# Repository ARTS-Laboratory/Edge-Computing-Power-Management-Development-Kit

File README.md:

# Edge-Computing-Power-Management-Development-Kit

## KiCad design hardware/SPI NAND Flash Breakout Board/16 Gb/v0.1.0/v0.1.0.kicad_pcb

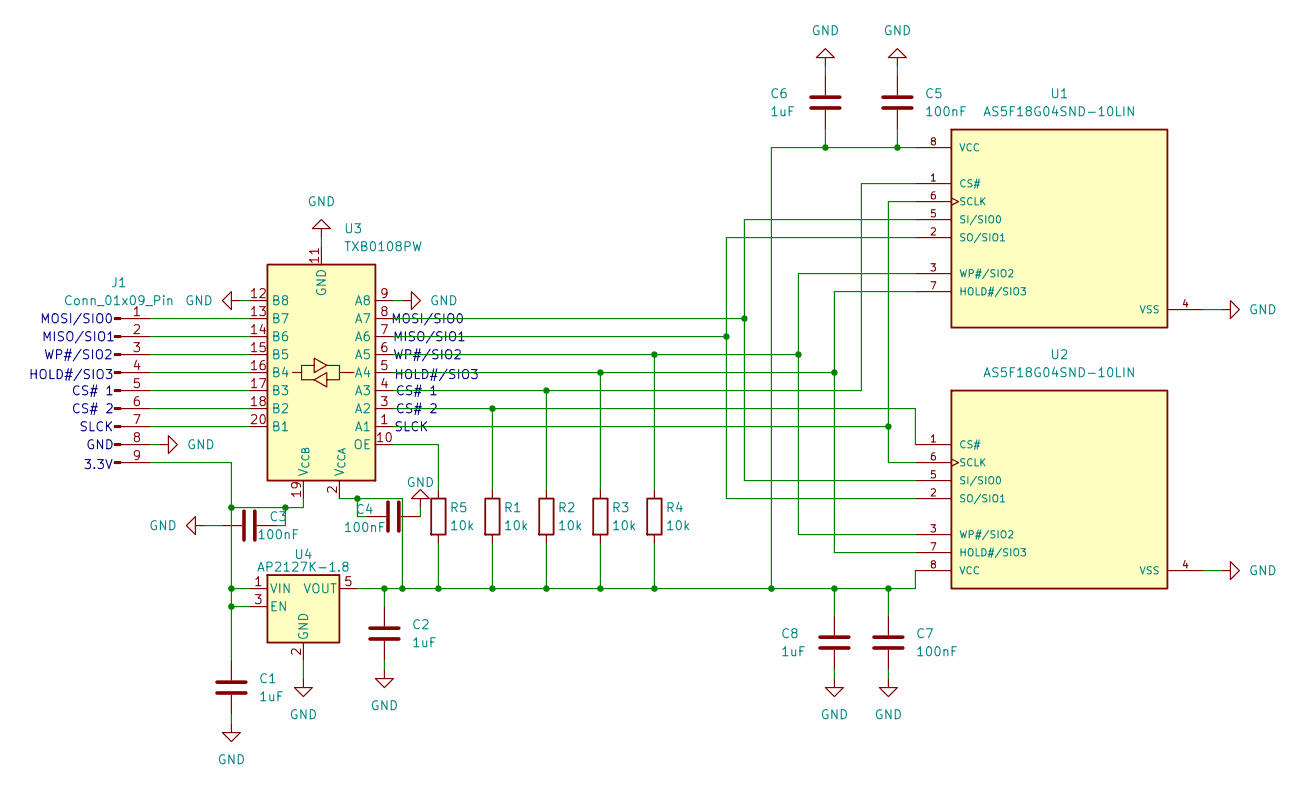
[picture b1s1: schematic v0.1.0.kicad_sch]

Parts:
C1, C2, C6, C8: 1uF; C_0805_2012Metric
C3, C4, C5, C7: 100nF; C_0805_2012Metric
J1: Conn_01x09_Pin; PinSocket_1x09_P2.54mm_Vertical
R1, R2, R3, R4, R5: 10k; R_0805_2012Metric
U1, U2: AS5F18G04SND-10LIN; SON127P600X800X80-8N; PARTREV 1.0; DigiKey_Part_Number 1450-AS5F18G04SND-10LIN-ND
U3: TXB0108PW; TSSOP-20_4.4x6.5mm_P0.65mm
U4: AP2127K-1.8; SOT-23-5

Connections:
GND: C1.2, C2.2, C3.1, C4.1, C5.1, C6.1, C7.2, C8.2, J1.8, U1.4 (VSS), U2.4 (VSS), U3.9 (A8), U3.11 (GND), U3.12 (B8), U4.2 (GND)
unnamed: J1.1, U3.13 (B7)
unnamed: J1.2, U3.14 (B6)
unnamed: J1.3, U3.15 (B5)
unnamed: J1.4, U3.16 (B4)
unnamed: J1.5, U3.17 (B3)
unnamed: J1.6, U3.18 (B2)
unnamed: J1.7, U3.20 (B1)
unnamed: C1.1, C3.2, J1.9, U3.19 (V_{CCB}), U4.1 (VIN), U4.3 (EN)
unnamed: R2.1, U1.1 (CS#), U3.4 (A3)
unnamed: R3.1, U1.7 (HOLD#/SIO3), U2.7 (HOLD#/SIO3), U3.5 (A4)
unnamed: U1.6 (SCLK), U2.6 (SCLK), U3.1 (A1)
unnamed: U1.5 (SI/SIO0), U2.5 (SI/SIO0), U3.8 (A7)
unnamed: U1.2 (SO/SIO1), U2.2 (SO/SIO1), U3.7 (A6)
unnamed: C2.1, C4.2, C5.2, C6.2, C7.1, C8.1, R1.2, R2.2, R3.2, R4.2, R5.2, U1.8 (VCC), U2.8 (VCC), U3.2 (V_{CCA}), U4.5 (VOUT)
unnamed: R4.1, U1.3 (WP#/SIO2), U2.3 (WP#/SIO2), U3.6 (A5)
unnamed: R1.1, U2.1 (CS#), U3.3 (A2)
unnamed: R5.1, U3.10 (OE)

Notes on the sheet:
WP#/SIO2
SLCK
CS# 1
CS# 2
GND
HOLD#/SIO3
MISO/SIO1
MOSI/SIO0
3.3V

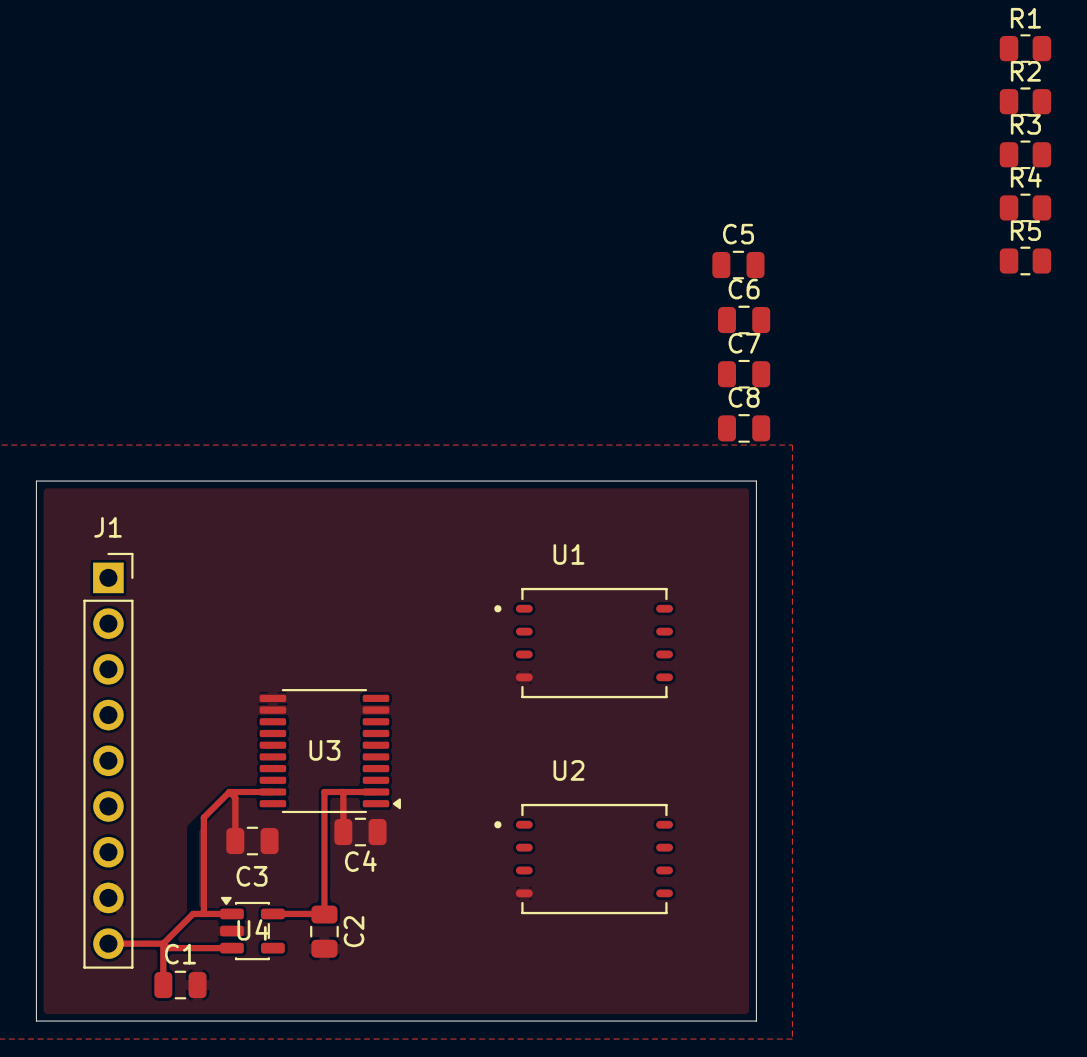
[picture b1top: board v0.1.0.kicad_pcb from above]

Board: 2 copper layers, 40.0 x 30.0 mm, 18 parts (0 on the bottom side), 18 nets.

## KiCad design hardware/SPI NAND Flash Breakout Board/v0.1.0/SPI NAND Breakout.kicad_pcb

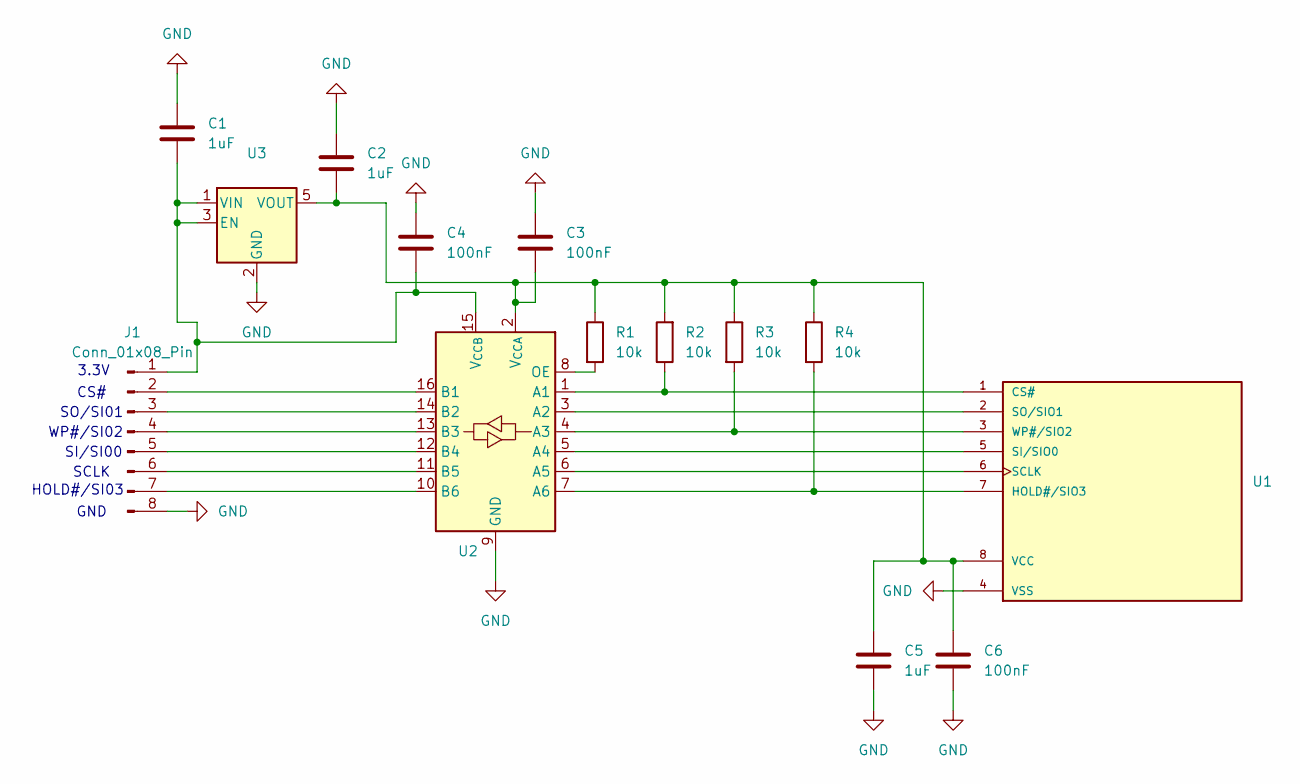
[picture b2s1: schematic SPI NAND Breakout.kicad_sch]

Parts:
C1, C2, C5: 1uF; C_0805_2012Metric
C3, C4, C6: 100nF; C_0805_2012Metric
J1: Conn_01x08_Pin; PinSocket_1x08_P2.54mm_Vertical
R1, R2, R3, R4: 10k; R_0805_2012Metric
U1: AS5F18G04SND-10LIN; SON127P600X800X80-8N; PARTREV 1.0
U2: TXB0106PW; TSSOP-16_4.4x5mm_P0.65mm
U3: AP2127K-1.8; SOT-23-5

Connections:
GND: C1.1, C2.1, C3.1, C4.1, C5.2, C6.2, J1.8, U1.4 (VSS), U2.9 (GND), U3.2 (GND)
unnamed: C1.2, C4.2, J1.1, U2.15 (V_{CCB}), U3.1 (VIN), U3.3 (EN)
unnamed: J1.2, U2.16 (B1)
unnamed: J1.3, U2.14 (B2)
unnamed: J1.4, U2.13 (B3)
unnamed: J1.5, U2.12 (B4)
unnamed: J1.6, U2.11 (B5)
unnamed: J1.7, U2.10 (B6)
unnamed: R2.1, U1.1 (CS#), U2.1 (A1)
unnamed: R4.2, U1.7 (HOLD#/SIO3), U2.7 (A6)
unnamed: U1.6 (SCLK), U2.6 (A5)
unnamed: U1.5 (SI/SIO0), U2.5 (A4)
unnamed: U1.2 (SO/SIO1), U2.3 (A2)
unnamed: C2.2, C3.2, C5.1, C6.1, R1.1, R2.2, R3.1, R4.1, U1.8 (VCC), U2.2 (V_{CCA}), U3.5 (VOUT)
unnamed: R3.2, U1.3 (WP#/SIO2), U2.4 (A3)
unnamed: R1.2, U2.8 (OE)

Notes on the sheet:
SO/SI01
WP#/SI02
SI/SI00
CS#
HOLD#/SI03
GND
3.3V
SCLK

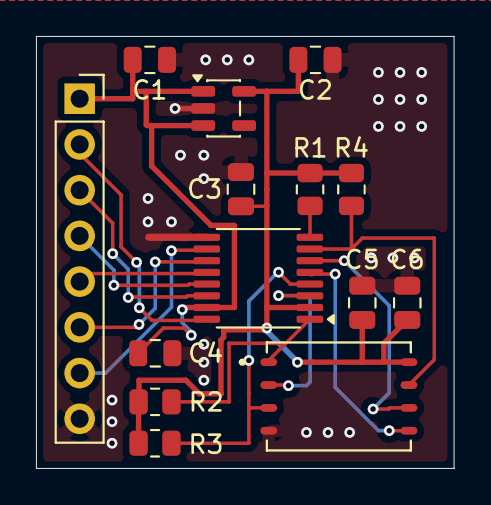
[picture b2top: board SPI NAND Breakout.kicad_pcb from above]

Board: 2 copper layers, 23.2 x 24.0 mm, 14 parts (0 on the bottom side), 16 nets.

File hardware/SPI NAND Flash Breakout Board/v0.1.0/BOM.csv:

Comment ,Designator,Footprint
1uF,"C1,C2,C5",Capacitor_SMD:C_0805_2012Metric
100nF,"C3,C4,C6",Capacitor_SMD:C_0805_2012Metric
Conn_01x08_Pin,J1,Connector_PinSocket_2.54mm:PinSocket_1x08_P2.54mm_Vertical
10k,"R1,R2,R3,R4",Resistor_SMD:R_0805_2012Metric
AS5F18G04SND-10LIN,U1,Breakout:SON127P600X800X80-8N
TXB0106PW,U2,Package_SO:TSSOP-16_4.4x5mm_P0.65mm
AP2127K-1.8,U3,Package_TO_SOT_SMD:SOT-23-5

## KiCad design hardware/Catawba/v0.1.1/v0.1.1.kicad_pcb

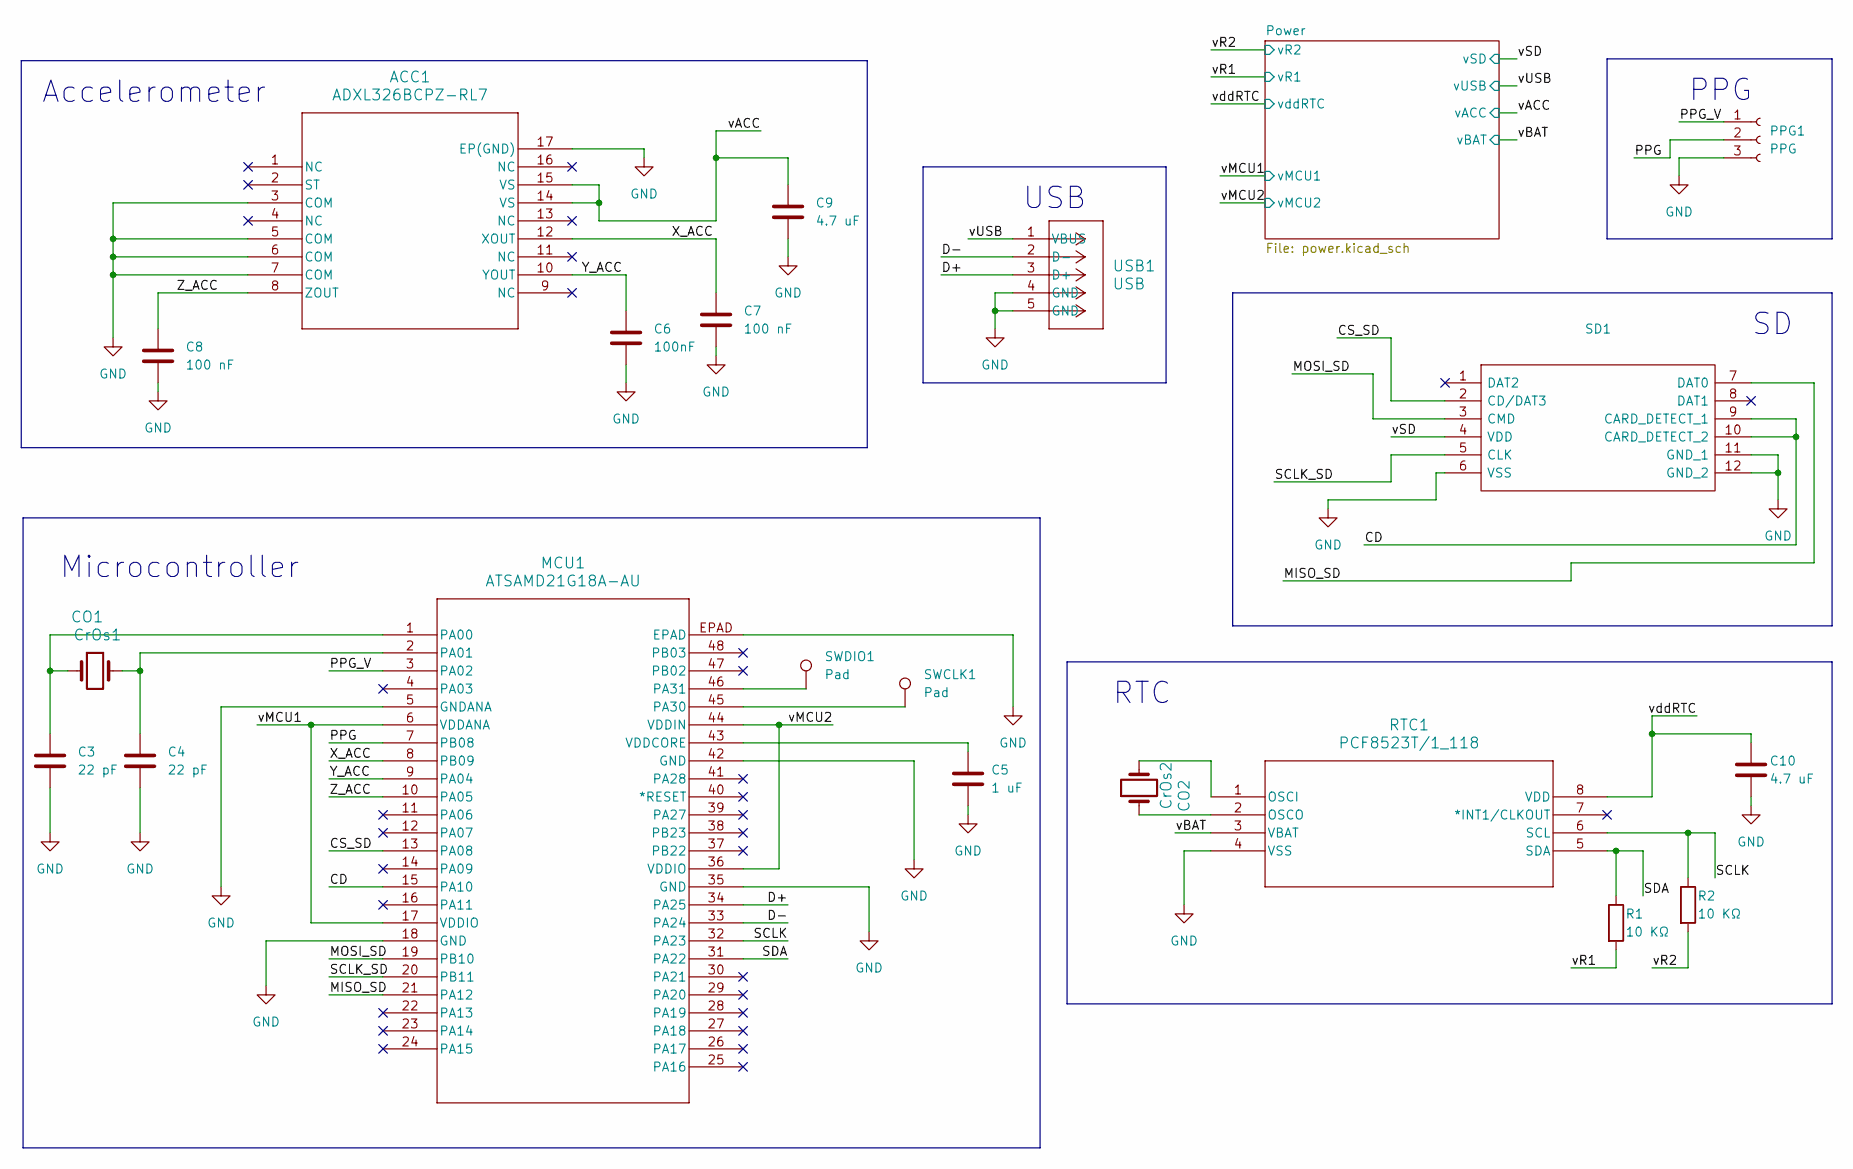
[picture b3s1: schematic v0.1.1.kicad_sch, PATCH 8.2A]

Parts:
ACC1: ADXL326BCPZ-RL7; LFCSP-16-1EP_4x4mm_P0.65mm_EP2.1x2.1mm
C3, C4: 22 pF; C_0603_1608Metric
C5: 1 uF; C_0603_1608Metric
C6: 100nF; C_0603_1608Metric
C7, C8: 100 nF; C_0603_1608Metric
C9, C10: 4.7 uF; C_0603_1608Metric
CO1: CrOs1; XTAL_ABS05-32.768KHZ
CO2: CrOs2; XTAL_ABS05-32.768KHZ
MCU1: ATSAMD21G18A-AU; TQFP-48-1EP_7x7mm_P0.5mm_EP3.5x3.5mm
PPG1: PPG; PinSocket_1x03_P2.54mm_Vertical
R1, R2: 10 KΩ; R_0603_1608Metric
RTC1: PCF8523T/1_118; SOIC-8_3.9x4.9mm_P1.27mm
SD1: TF-00B1; MicroSD_Socket; Manufacturer_Part_Number 1660; Mouser Part Number 485-1660
SWCLK1: Pad; TestPoint_Pad_D2.5mm
SWDIO1: Pad; TestPoint_Pad_D2.5mm
USB1: USB; USB_Micro-B_Molex-105017-0001

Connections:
/CD: MCU1.15 (PA10), SD1.9 (CARD_DETECT_1), SD1.10 (CARD_DETECT_2)
/CS_SD: MCU1.13 (PA08), SD1.2 (CD/DAT3)
/D+: MCU1.34 (PA25), USB1.3 (D+)
/D-: MCU1.33 (PA24), USB1.2 (D-)
/MISO_SD: MCU1.21 (PA12), SD1.7 (DAT0)
/MOSI_SD: MCU1.19 (PB10), SD1.3 (CMD)
/PPG: MCU1.7 (PB08), PPG1.2
/PPG_V: MCU1.3 (PA02), PPG1.1
/SCLK: MCU1.32 (PA23), R2.1, RTC1.6 (SCL)
/SCLK_SD: MCU1.20 (PB11), SD1.5 (CLK)
/SDA: MCU1.31 (PA22), R1.1, RTC1.5 (SDA)
/X_ACC: ACC1.12 (XOUT), C7.1, MCU1.8 (PB09)
/Y_ACC: ACC1.10 (YOUT), C6.1, MCU1.9 (PA04)
/Z_ACC: ACC1.8 (ZOUT), C8.1, MCU1.10 (PA05)
/vACC: ACC1.14 (VS), ACC1.15 (VS), C9.1, C10.1, MCU1.6 (VDDANA), MCU1.17 (VDDIO), MCU1.36 (VDDIO), MCU1.44 (VDDIN), R1.2, R2.2, RTC1.8 (VDD), SD1.4 (VDD); also elsewhere on the board
/vBAT: RTC1.3 (VBAT); also elsewhere on the board
/vUSB: USB1.1 (VBUS); also elsewhere on the board
GND: ACC1.3 (COM), ACC1.5 (COM), ACC1.6 (COM), ACC1.7 (COM), ACC1.17 (EP(GND)), C3.2, C4.2, C5.2, C6.2, C7.2, C8.2, C9.2, C10.2, MCU1.5 (GNDANA), MCU1.18 (GND), MCU1.35 (GND), MCU1.42 (GND), MCU1.EPAD, PPG1.3, RTC1.4 (VSS), SD1.6 (VSS), SD1.11 (GND_1), SD1.12 (GND_2), USB1.4 (GND), USB1.5 (GND); also elsewhere on the board
unnamed: C3.1, CO1.1, MCU1.1 (PA00)
unnamed: C4.1, CO1.2, MCU1.2 (PA01)
unnamed 20: MCU1.45 (PA30), SWCLK1.1; also elsewhere on the board
unnamed 21: MCU1.46 (PA31), SWDIO1.1; also elsewhere on the board
unnamed: C5.1, MCU1.43 (VDDCORE)
unnamed: CO2.2, RTC1.1 (OSCI)
unnamed: CO2.1, RTC1.2 (OSCO)

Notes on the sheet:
PPG
USB
Accelerometer
Microcontroller
RTC

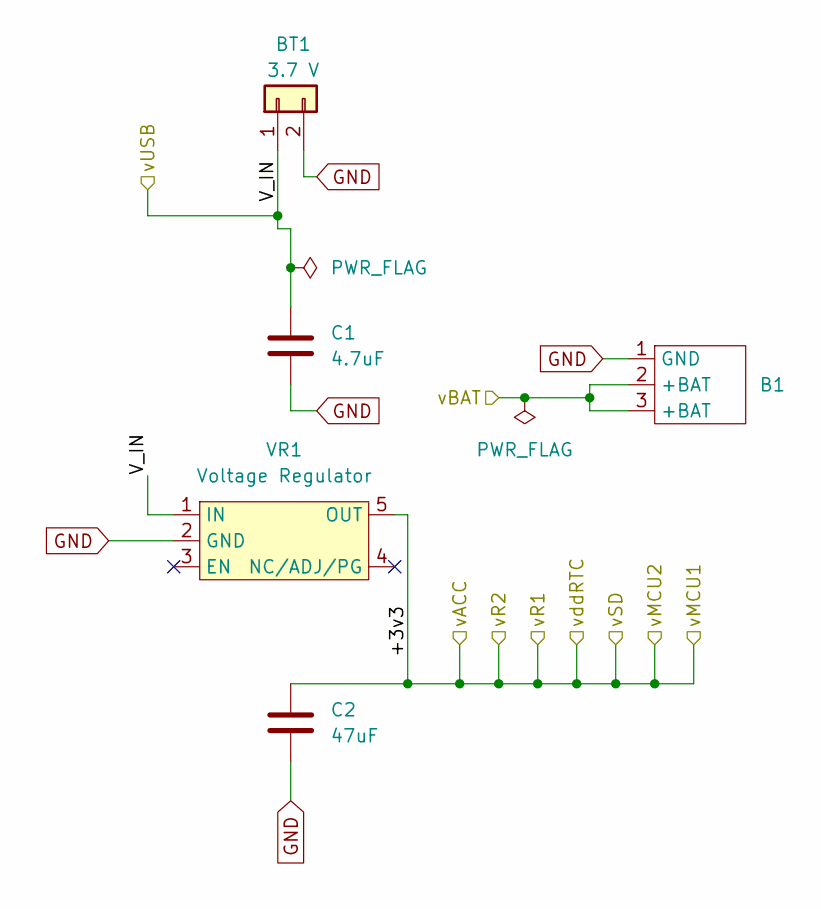
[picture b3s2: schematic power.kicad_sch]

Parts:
B1: 3000; Battery
BT1: 3.7 V; PinHeader_1x02_P2.00mm_Vertical
C1: 4.7uF; C_0603_1608Metric
C2: 47uF; C_1210_3225Metric
VR1: Voltage Regulator; TSOP5_NCP711_ONS

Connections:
/vACC: C2.1, VR1.5 (OUT); also elsewhere on the board
/vBAT: B1.2 (+BAT), B1.3 (+BAT); also elsewhere on the board
/vUSB: BT1.1, C1.1, VR1.1 (IN); also elsewhere on the board
GND: B1.1 (GND), BT1.2, C1.2, C2.2, VR1.2 (GND); also elsewhere on the board

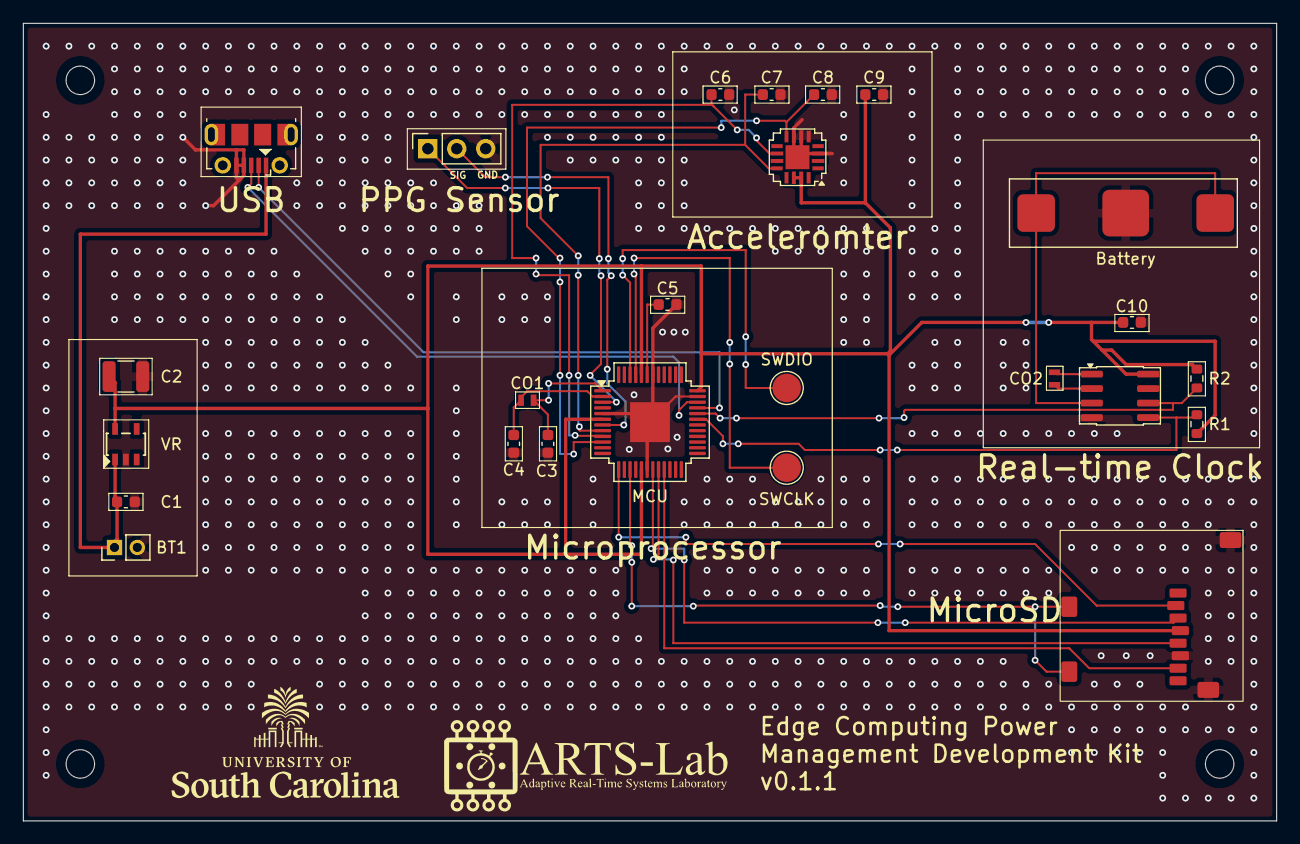
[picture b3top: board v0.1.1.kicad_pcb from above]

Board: 2 copper layers, 110.0 x 70.0 mm, 25 parts (0 on the bottom side), 25 nets.

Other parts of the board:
SWCLK: Pad; TestPoint_Pad_D2.5mm
SWDIO: Pad; TestPoint_Pad_D2.5mm

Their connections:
unnamed 20: SWCLK.1; also elsewhere on the board
unnamed 21: SWDIO.1; also elsewhere on the board

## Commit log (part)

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2026-03-13 initial push
2026-04-15 Add files via upload
    V1.0
2026-04-15 Delete PATCH_GO_5 directory
    I will reupload with better names.
2026-04-15 Add files via upload
    V1.0 - Next updates, draw large white boxes around the important component groups, including putting battery and RTC near each other and in the same box.
2026-04-15 Add files via upload
    Images of V1.0
2026-04-16 test: working locally and pushing
2026-04-16 Test
2026-04-16 rename V1.0 to v0.1
2026-04-16 deleting DS_store
2026-04-16 test for updating pcb
2026-04-16 test again
2026-04-16 organization
2026-04-16 created v0.1.1
2026-04-16 moved components
2026-04-22 White Boxes
2026-04-27 Ground plane
2026-05-05 Moved resistors
    Now they are connected properly to SDA, SCL, and VCC.
2026-05-05 Added photos
2026-05-07 created hardware folder
2026-05-07 added v0.1.1 to silk screen
2026-05-13 Added BOM
2026-05-18 Edit Bill of Materials
2026-05-18 updates on bill of materials
2026-05-18 BOM edits
2026-05-18 Update Bill_of_materials_v0.1.1.xlsx
    removed (digikey) from vendor one. They are preferred, but not always vendor 1.
    Asutin
2026-05-19 Creation of v0.1.2
    Not sure if the HDK in the mail will work. Patrick and I have thoughts on how to improve it. I didn't design pads for the sensors to go on. The 0.3mm traces may be too small, and we may also have to 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
2026-05-19 Added Ordered Tab
2026-05-19 Updates for BOM
2026-05-24 uUpdatesto BOM post order.
2026-05-24 updates to BOM post order
2026-05-25 cleanup
2026-05-25 BOM updates
2026-05-26 Update Bill_of_materials_v0.1.1.xlsx
    added mouser parts
2026-05-26 Order Received
2026-05-26 change
2026-05-27 new folder
2026-05-28 shunt notes
2026-06-02 Added pictures of PCB for debug
    I don't see any faulty traces or solder bridges. Still exploring those options while trying to see if it was something else
2026-06-02 moved USB on v0.1.2
2026-06-03 Update references
2026-06-03 Update pin electrical type MCU1
2026-06-03 Pin updates and power fixes
2026-06-08 Edit code to make PPG sensor turn on
2026-06-08 Added Sheet - HDK Kit
2026-06-15 Data Collection
2026-06-23 photos
